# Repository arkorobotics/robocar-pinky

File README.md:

# Robocar - Pinky	

## Intro
Pinky is a 1/16 scale DIY autonomous car designed to compete in the [DIY Robocar](https://diyrobocars.com) race. Pinky also has a counterpart testbed named [Brain](Brain).

## Design

### Block Diagram

### Assembled Hardware

## Software

See the [Software](./Software) subfolder.

## Hardware

### Perception System
Part | Cost  |  Link
------------ | ------------- | -------------
ZED Mini | $399.00 | [Stereo Labs Store](https://store.stereolabs.com/products/zed-mini)
IMX219 Camera Module (Fisheye) | $29.99  | [Amazon](https://www.amazon.com/gp/product/B07VFFRX4C)

### Compute Element
Part | Cost  |  Link
------------ | ------------- | -------------
NVIDIA Jetson Nano Developer Kit | $98.98 | [Amazon](https://www.amazon.com/gp/product/B07PZHBDKT/)
Intel Dual Band Wireless-Ac 8265 w/ BT Module | $21.55 | [Amazon](https://www.amazon.com/Intel-Dual-Band-Wireless-Ac-8265/dp/B01MZA1AB2)
Noctua Fan | $14.95 | [Amazon](https://www.amazon.com/gp/product/B071FNHVXN)

### Hardware Interface Board
Part | Cost  |  Link
------------ | ------------- | -------------
Glue Board (Fab/Assembly Required) | ~$300.00 | [GitHub](./Electronics/Glue%20Board)

### Drive System
Part | Cost  |  Link
------------ | ------------- | -------------
VATOS RC Car 9137R | $54.99 | [Amazon](https://www.amazon.com/gp/product/B07QRRJZDG/)

### Chassis
Part | Cost | Link
------------ | ------------- | -------------
Screw Set | $20.98 | [Amazon](https://www.amazon.com/gp/product/B07QLWPJKC/)
Threaded Heat Insert | $19.99 | [Amazon](https://www.amazon.com/gp/product/B07MWBJB67)
3D Printable Models (Fab/Assembly Required) | ~$20.00 | [GitHub](./Mechanical/CAD/STL%20Files)

### Other
Part | Cost  |  Link
------------ | ------------- | -------------
ENGPOW 7.4V 3000mah 30C Lipo Battery | $22.99 | [Amazon](https://www.amazon.com/gp/product/B075QDPSDQ/)
Samsung SD Car 128GB | $16.99 | [Amazon](https://www.amazon.com/gp/product/B06XWZWYVP/)
1.5 ft/50cm Micro USB 3.0 Cable | $8.79 | [Amazon](https://www.amazon.com/gp/product/B075CL915V/)
5V/4A 20W Switching Power | $8.99 | [Amazon](https://www.amazon.com/gp/product/B01N4HYWAM/)
WiFi/BT Antennas | $13.99 | [Amazon](https://www.amazon.com/gp/product/B01E29566W/)
USB 3.1 Right Angle A to Right Angle C | $19.25 | [UsbFirewire](https://www.usbfirewire.com/parts/rr-arch-xxg.html#RR-ARCH-10GRC)

### Harnessing

## Assembly

For 3D printed models, use the [Autodesk Fusion 360 Pinky CAD](./Mechanical/CAD/Pinky%20Assembly%20v27.f3z) model for assembly.

For electrical assembly, see diagram below:

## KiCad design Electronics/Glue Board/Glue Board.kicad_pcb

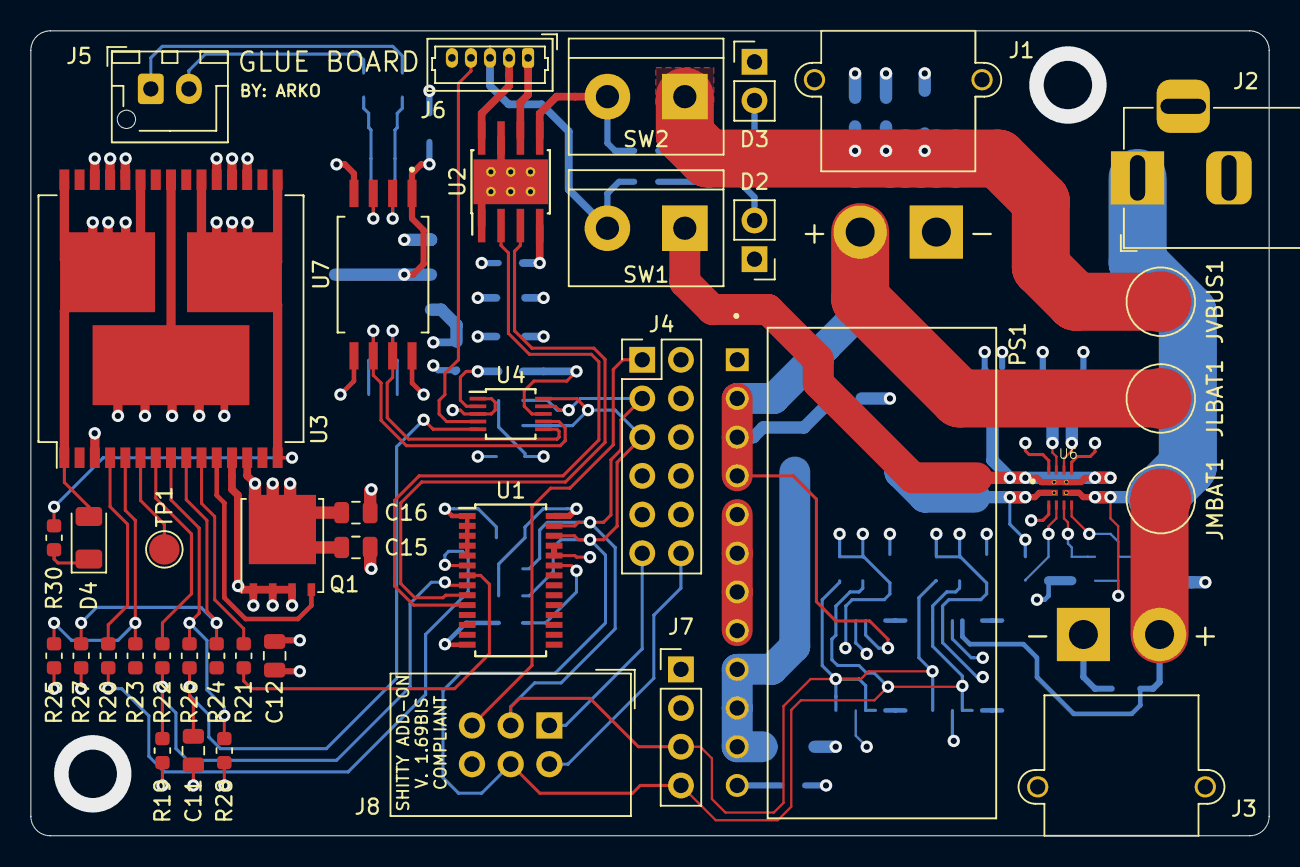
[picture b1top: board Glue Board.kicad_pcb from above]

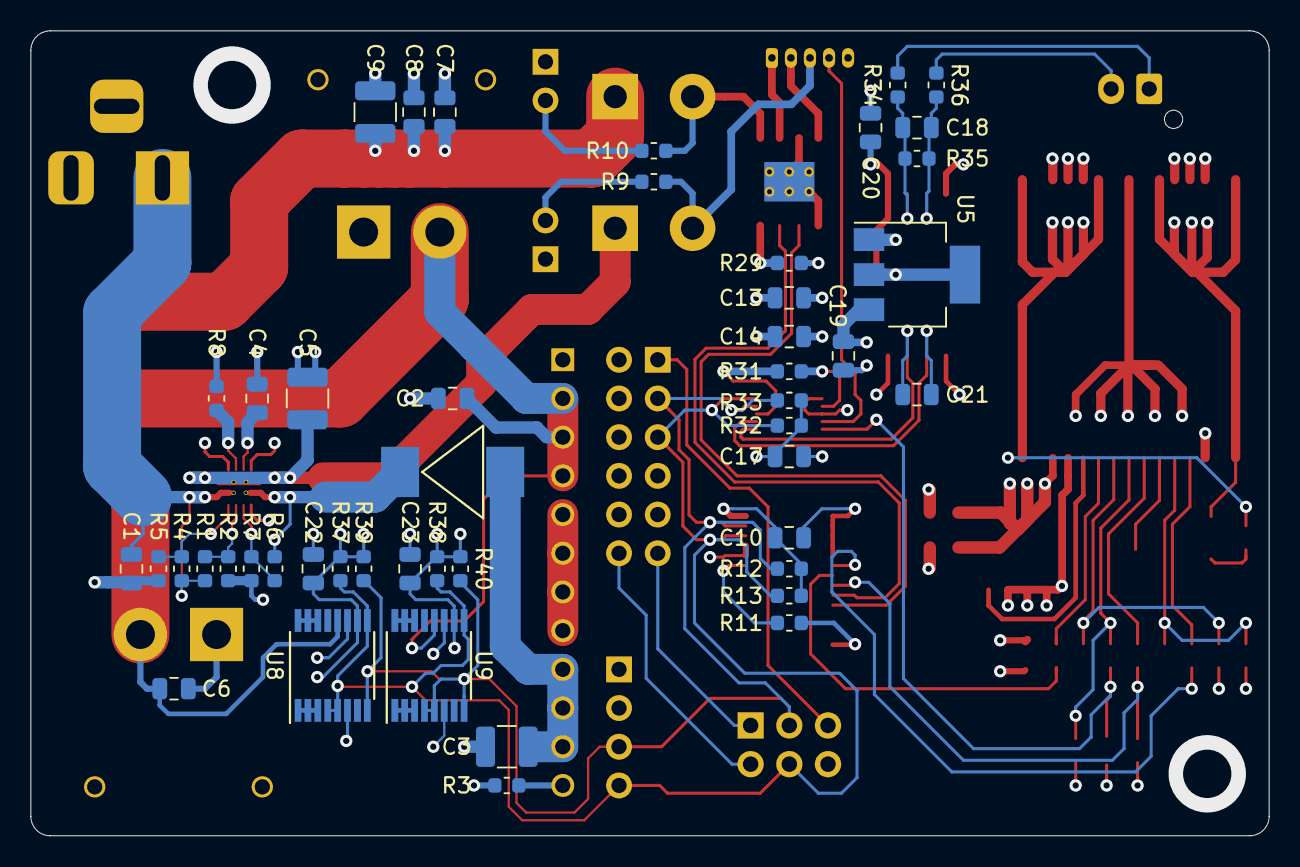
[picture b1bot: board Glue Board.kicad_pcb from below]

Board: 4 copper layers, 81.3 x 52.8 mm, 87 parts (47 on the bottom side), 56 nets.

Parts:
C1, C2, C4, C6, C7, C17, C22, C23: 1uF; C_0805_2012Metric
C3, C5, C9: 100uF; C_1210_3225Metric
C8, C19, C20: 10uF; C_0805_2012Metric
C10, C12, C14, C16: 0.1uF; C_0805_2012Metric
C11, C18, C21: 33nF; C_0805_2012Metric
C13: 22uF; C_0805_2012Metric
C15: 47uF; C_0805_2012Metric
D1: STPS5L60S; DO-214AB-SMC
D2, D3: LED; PinHeader_1x02_P2.54mm_Vertical
D4: LED_Dual_2pin; LED_1206_3216Metric
J1, J3: Conn_01x02_Male; AMASS_XT30PW-M_1x02_P2.50mm_Horizontal
J2: Barrel_Jack; BarrelJack_Horizontal
J4: Conn_02x06_Odd_Even; PinHeader_2x06_P2.54mm_Vertical
J5: Conn_01x02_Male; JST_XH_B2B-XH-AM_1x02_P2.50mm_Vertical
J6: Conn_01x05_Female; Molex_PicoBlade_53047-0510_1x05_P1.25mm_Vertical
J7: Conn_01x04_Male; PinHeader_1x04_P2.54mm_Vertical
J8: Conn_02x03_Odd_Even; IDC-Header_2x03_P2.54mm_Vertical
JLBAT1: TestPoint; TestPoint_Pad_D4.0mm
JMBAT1: TestPoint; TestPoint_Pad_D4.0mm
JVBUS1: TestPoint; TestPoint_Pad_D4.0mm
PS1: R-745.0D; CONV_R-745.0D
Q1: CSD17501Q5A; TDSON-8-1
R1, R6: 23.7k; R_0603_1608Metric
R2, R5, R7: 5k; R_0603_1608Metric
R3: 2.6k; R_0603_1608Metric
R4: 10.2k; R_0603_1608Metric
R8: 18.7k; R_0603_1608Metric
R9: 47R; R_0603_1608Metric
R10: 470; R_0603_1608Metric
R11, R12, R13, R19, R26, R31, R32, R33, R34, R36, R37, R38, R39, R40: 10k; R_0603_1608Metric
R20, R21, R22, R23, R24, R28: 1k; R_0603_1608Metric
R25, R27, R30: 4.7k; R_0603_1608Metric
R29: 30K; R_0603_1608Metric
R35: 470R; R_0603_1608Metric
SW1, SW2: SW_SPST; TerminalBlock_bornier-2_P5.08mm
TP1: TestPoint; TestPoint_Pad_D2.0mm
U1: PCA9685PW; TSSOP-28_4.4x9.7mm_P0.65mm
U2: DRV8871DDA; Texas_HTSOP-8-1EP_3.9x4.9mm_P1.27mm_EP2.95x4.9mm_Mask2.4x3.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
U3: VNH5019ATR-E; ST_MultiPowerSO-30
U4: ADS1115IDGS; TSSOP-10_3x3mm_P0.5mm
U5: NCP1117-5.0_SOT223; SOT-223-3_TabPin2
U6: TPS2121RUXR; IC_TPS2121RUXR
U7: AMC1301DWVR; SOIC127P1150X280-8N
U8, U9: INA260; TSSOP-16_4.4x5mm_P0.65mm

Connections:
+3.3V: J4.1, J8.5
+5V: C10.1, C17.1, C22.1, C23.1, J4.2, J4.4, J6.3, J7.1, R9.1, R12.1, R13.1, R25.1, R27.1, R31.1, R32.1, R33.1, R37.1, R38.1, R39.1, R40.1, SW1.2, U1.28, U4.8, U7.8, U8.10, U9.10
+5VA: C20.1, U5.2, U7.1
DRIVE_CS_ADC: C11.1, R26.2, U4.5
DRIVE_PWM: R19.1, R22.2, U1.8
GND: C1.2, C2.2, C3.2, C4.2, C5.2, C6.2, C7.2, C8.2, C9.2, C10.2, C11.2, C12.2, C13.2, C14.2, C15.2, C16.2, C17.2, C19.2, C20.2, C22.2, C23.2, D2.1, D3.1, J1.1, J2.2, J3.1, J4.6, J4.9, J6.5, J7.2, J8.6, PS1.5, PS1.6, PS1.7, PS1.8, R2.2, R3.2, R5.2, R7.2, R8.2, R11.1, R19.2, R28.2, R29.2, U1.1, U1.2, U1.3, U1.4, U1.5, U1.14, U1.24, U1.25, U2.1, U2.7, U2.9, U3.18, U3.19, U3.20, U3.26, U3.27, U3.28, U4.1, U4.3, U5.1, U6.3, U6.9, U6.12, U7.4, U7.5, U8.6, U8.11, U9.6, U9.11
GPIO50: J4.11, J8.1
GPIO79: J4.12, J8.2
IN1: U1.9, U2.3
IN2: U1.10, U2.2
INA: R20.2, U1.6
INB: R21.2, U1.7
unnamed: C1.1, J2.1, R1.1, R4.1, U6.7, U6.7_1
unnamed: C3.1, D1.2, PS1.9, PS1.10, PS1.11
unnamed: C4.1, U6.11
unnamed: C5.1, SW1.1, U6.1, U6.1_1, U6.8, U6.8_1
unnamed: C7.1, C8.1, C9.1, JVBUS1.1, SW2.1
unnamed: C18.1, R34.2, R35.1, U7.2
unnamed: C18.2, R35.2, R36.1, U7.3
unnamed: D1.1, R6.1, U6.2, U6.2_1
unnamed: D2.2, R9.2
unnamed: D3.2, R10.2
unnamed: D4.1, R30.1
unnamed: J6.1, U2.6
unnamed: J6.2, U2.8
unnamed: PS1.12, R3.1
unnamed: Q1.4, U3.11
unnamed: R1.2, R2.1, U6.5
unnamed: R4.2, R5.1, U6.6
unnamed: R6.2, R7.1, U6.4
unnamed: R8.1, U6.10
unnamed: R11.2, U1.23
unnamed: R20.1, U3.4
unnamed: R21.1, U3.10
unnamed: R22.1, U3.7
unnamed: R23.1, R25.2, U3.5
unnamed: R24.1, R27.2, U3.9
unnamed: R26.1, R28.1, U3.8
unnamed: R29.1, U2.4
unnamed: R31.2, U4.2
unnamed: TP1.1, U3.6
unnamed: U8.1, U8.2, U8.3
unnamed: U8.14, U8.15, U8.16
unnamed: U9.1, U9.2, U9.3
unnamed: U9.14, U9.15, U9.16
OUTA: D4.2, J5.1, R34.1, U3.1, U3.25, U3.30, U3.33
OUTB: J5.2, R30.2, R36.2, U3.15, U3.16, U3.21, U3.32
SCL: J4.5, J7.4, J8.4, R13.2, R32.2, R37.2, R38.2, U1.26, U4.10, U8.4, U8.5, U8.9, U9.9
SDA: J4.3, J7.3, J8.3, R12.2, R33.2, R39.2, R40.2, U1.27, U4.9, U8.8, U9.4, U9.5, U9.8
STEERING_POS_ADC: J6.4, U4.4
VBUS: C12.1, C13.1, C14.1, C19.1, Q1.1, Q1.2, Q1.3, R10.1, SW2.2, U2.5, U3.12, U5.3
VCC: C15.1, C16.1, Q1.5, U3.3, U3.13, U3.23, U3.31
VLOGIC_BAT: C2.1, J1.2, JLBAT1.1, PS1.2, PS1.3, PS1.4, U9.12
VMOTOR_BAT: C6.1, J3.2, JMBAT1.1, U8.12
VMOTOR_N_ADC: C21.2, U4.7, U7.6
VMOTOR_P_ADC: C21.1, U4.6, U7.7

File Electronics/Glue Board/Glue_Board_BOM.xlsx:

Reference | Quantity | Value | Footprint | Datasheet | MPN
C11 C18 C21 | 3 | 33nF | Capacitor_SMD:C_0805_2012Metric | ~ | C0805C333K5RACTU
C13 | 1 | 22uF | Capacitor_SMD:C_1210_3225Metric | ~ | C1210C226K3PACTU
C15 | 1 | 47uF | Capacitor_SMD:C_1210_3225Metric | ~ | GRM32EC81C476KE15L
C16 C12 C14 C10 | 4 | 0.1uF | Capacitor_SMD:C_0805_2012Metric | ~ | C0805C104Z5VACTU
C4 C1 C2 C7 C6 C17 C23 C22 | 8 | 1uF | Capacitor_SMD:C_0805_2012Metric | ~ | C0805C105K4RACTU
C5 C3 C9 | 3 | 100uF | Capacitor_SMD:C_1210_3225Metric | ~ | C1210C107M4PAC7800
C8 C20 C19 | 3 | 10uF | Capacitor_SMD:C_0805_2012Metric | ~ | C0805C106K4PACTU
D1 | 1 | STPS5L60S | agg:DO-214AB-SMC | ~ | STPS5L60S
D2 | 1 | LED | Connector_PinHeader_2.54mm:PinHeader_1x02_P2.54mm_Vertical | ~ | MPR3BWD
D3 | 1 | LED | Connector_PinHeader_2.54mm:PinHeader_1x02_P2.54mm_Vertical | ~ | MPR3RD
D4 | 1 | LED_Dual_2pin | LED_SMD:LED_1206_3216Metric | ~ | LTST-C235KGKRKT
J1 J3 | 2 | Conn_01x02_Male | Connector_AMASS:AMASS_XT30PW-M_1x02_P2.50mm_Horizontal | ~ | XT30PW-M
J2 | 1 | Barrel_Jack | Connector_BarrelJack:BarrelJack_Horizontal | ~ | PJ-102B
J4 | 1 | Conn_02x06_Odd_Even | Connector_PinHeader_2.54mm:PinHeader_2x06_P2.54mm_Vertical | ~ | 67997-112HLF
J5 | 1 | Conn_01x02_Male | Connector_JST:JST_XH_B2B-XH-AM_1x02_P2.50mm_Vertical | ~ | B2B-XH-A(LF)(SN)
J6 | 1 | Conn_01x05_Female | Connector_Molex:Molex_PicoBlade_53047-0510_1x05_P1.25mm_Vertical | ~ | 530470510
J7 | 1 | Conn_01x04_Male | Connector_PinHeader_2.54mm:PinHeader_1x04_P2.54mm_Vertical | ~
J8 | 1 | Conn_02x03_Odd_Even | Connector_IDC:IDC-Header_2x03_P2.54mm_Vertical | ~ | SFH11-NBPC-D03-ST-BK
JLBAT1 JVBUS1 JMBAT1 | 3 | TestPoint | TestPoint:TestPoint_Pad_D4.0mm | ~
PS1 | 1 | R-745.0D | libs:CONV_R-745.0D | Manufacturer Recommendations | R-745.0D
Q1 | 1 | CSD17501Q5A | Package_TO_SOT_SMD:TDSON-8-1 | http://www.ti.com/lit/gpn/csd17501q5a | CSD17501Q5A
R1 R6 | 2 | 23.7k | Resistor_SMD:R_0603_1608Metric | ~ | RC0603FR-0723K7L
R10 | 1 | 470 | Resistor_SMD:R_0603_1608Metric | ~ | ESR03EZPJ471
R19 R26 R11 R13 R12 R31 R32 R33 R34 R36 R39 R37 R40 R38 | 14 | 10k | Resistor_SMD:R_0603_1608Metric | ~ | RC0603FR-0710KL
R2 R7 R5 | 3 | 5k | Resistor_SMD:R_0603_1608Metric | ~ | CR0603-FX-4991ELF
R25 R27 R30 | 3 | 4.7k | Resistor_SMD:R_0603_1608Metric | ~ | ERJ-3EKF4751V
R28 R22 R21 R20 R23 R24 | 6 | 1k | Resistor_SMD:R_0603_1608Metric | ~ | RC0603JR-071KL
R29 | 1 | 30K | Resistor_SMD:R_0603_1608Metric | ~ | ERA-3AEB303V
R3 | 1 | 2.6k | Resistor_SMD:R_0603_1608Metric | ~ | RC0603FR-072K61L
R35 | 1 | 470R | Resistor_SMD:R_0603_1608Metric | ~ | ESR03EZPJ471
R4 | 1 | 10.2k | Resistor_SMD:R_0603_1608Metric | ~ | RC0603FR-0710K2L
R8 | 1 | 18.7k | Resistor_SMD:R_0603_1608Metric | ~ | RC0603FR-0718K7L
R9 | 1 | 47R | Resistor_SMD:R_0603_1608Metric | ~ | ESR03EZPJ470
SW1 | 1 | SW_SPST | TerminalBlock:TerminalBlock_bornier-2_P5.08mm | ~ | M2011LL1W01-G
SW2 | 1 | SW_SPST | TerminalBlock:TerminalBlock_bornier-2_P5.08mm | ~ | M2011LL1W01-C
TP1 | 1 | TestPoint | TestPoint:TestPoint_Pad_D2.0mm | ~
U1 | 1 | PCA9685PW | Package_SO:TSSOP-28_4.4x9.7mm_P0.65mm | http://www.nxp.com/documents/data_sheet/PCA9685.pdf | PCA9685PW/Q900,118
U2 | 1 | DRV8871DDA | Package_SO:Texas_HTSOP-8-1EP_3.9x4.9mm_P1.27mm_EP2.95x4.9mm_Mask2.4x3.1mm_Therm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 | http://www.ti.com/lit/ds/symlink/drv8871.pdf | DRV8871DDAR
U3 | 1 | VNH5019ATR-E | Package_SO:ST_MultiPowerSO-30 | https://www.st.com/resource/en/datasheet/vnh5019a-e.pdf | VNH5019ATR-E
U4 | 1 | ADS1115IDGS | Package_SO:TSSOP-10_3x3mm_P0.5mm | http://www.ti.com/lit/ds/symlink/ads1113.pdf | ADS1115IDGSR
U5 | 1 | NCP1117-5.0_SOT223 | Package_TO_SOT_SMD:SOT-223-3_TabPin2 | http://www.onsemi.com/pub_link/Collateral/NCP1117-D.PDF | NCP1117LPST50T3G
U6 | 1 | TPS2121RUXR | libs:IC_TPS2121RUXR | TEXAS INSTRUMENTS | TPS2121RUXR
U7 | 1 | AMC1301DWVR | libs:SOIC127P1150X280-8N | TEXAS INSTRUMENTS | AMC1301DWVR
U8 U9 | 2 | INA260 | Package_SO:TSSOP-16_4.4x5mm_P0.65mm | http://www.ti.com/lit/ds/symlink/ina260.pdf | INA260AIPW

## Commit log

2019-12-26 Initial commit with block diagram
    Initial commit with block diagram
2019-12-26 Updated with block diagram and bill of materials
    Updated with block diagram and bill of materials
2019-12-27 Started "Glue Board" PCB
    Started "Glue Board" PCB
2019-12-28 Finished the schematic for the most parts
    Finished the schematic for the most parts
2019-12-29 Complete Schematic and BOM
    Complete Schematic and BOM. Next up, layout!
2019-12-30 Added Motor v-sense and battery mon. Layout time!
    Added Motor v-sense and battery mon. Layout time!
2019-12-31 Glue Board - Rev A - Production
    Glue Board - Rev A - Production
2020-01-02 added oCamS Software
2020-01-02 Failed attempted to use opencv4. Next, I'm going to try installing opencv3 and modifying the ROS example back to the original config
2020-01-05 Abandoning the oCamS stereo cam and switching to ZED Mini due to support issues with Ubuntu 18 and ROS Melodic.
2020-01-22 Abandoned oCamS for ZED Mini and updated Glue Board
    Abandoned oCamS for ZED Mini and updated Glue Board
2020-01-25 Updated Readme
    Updated Readme
2020-01-25 Fixed spacing
    Fixed spacing
2020-01-27 Added harnessing and assembly diagrams
    Added harnessing and assembly diagrams
2020-01-27 Added broken software
2020-01-27 Started rc_ctrl. Working i2c example build
2020-01-27 Clean up
2020-01-27 some repairs
2020-01-27 more repairs
2020-01-27 renaming
2020-01-27 cleaned up more
2020-01-29 Added raw open source libraries for the i2c devices
    Added raw open source libraries for the i2c devices. Next step is to modify them to work with the i2c libraries.
2020-01-31 Ported INA260 for testing
    Ported INA260 for testing
2020-02-01 Working voltage measurement using INA260 via I2C
2020-02-03 Initial attempt at porting all the i2c device libraries
    Initial attempt at porting all the i2c device libraries
2020-02-03 All i2c device libraries build and have undergone minimal testing. Next up... real testing
2020-02-05 Fixed 8bit/16bit read/write error. Next step is to propagate these changes to other functions within the project
2020-02-05 Patched the 8/16bit word issue with I2C R/W
    Patched the 8/16bit word issue with I2C R/W
2020-02-05 Working PWM. ADS1115 still giving bogus values.
2020-02-06 Working ADC1115! It was mostly a schematic error.
2020-02-06 Removed .o file...i really should add a gitignore
2020-02-06 Added schematic change notes for REV B
    Added schematic change notes for REV B
2020-02-06 Added robocar stand
    Added robocar stand
2020-02-09 Moved glue board test code into glue.c
    Moved glue board test code into glue.c. More coding/testing required.
2020-02-11 First ctrl system test
    First ctrl system test
2020-02-11 Functional wheel spin code!
2020-02-11 Modified I2C to run faster by increasing the clock speed and decreasing the delay time between r/w
2020-02-11 Updated readme to reflect changes to jetson i2c config
    Updated readme to reflect changes to jetson i2c config
2020-02-11 Updated i2c to use 100us delays
    Updated i2c to use 100us delays
2020-02-12 First attempt at making a monotonic soft timer based control loop
    First attempt at making a monotonic soft timer based control loop
2020-02-12 Taking a step back
    Taking a step back
2020-02-12 minor bug fix
2020-02-13 Here we go again...
    Here we go again...
2020-02-14 Fixed C/C++ makefile errors
2020-02-14 Compiled/running soft real time loop
2020-02-14 removed swp artifact
2020-02-14 Working 50Hz control codegit add -A!
2020-02-16 Added shared memory, but there's a lot left to do
    Added shared memory, but there's a lot left to do
2020-02-16 Added c&dh python script and demonstrated shared mem with semaphones for transfering data between ctrl and cdh
2020-02-16 A little clean up and test before major additions
    A little clean up and test before major additions
2020-02-16 Clean up complete. Next up? python decode/write/print, then PID controller
2020-02-17 Packet parsing test
    Packet parsing test
2020-02-17 Working C++/Python command/telem. Next is PID, then python overhaul to interface with user/prcp
2020-02-17 Added state machine and fault protection
    Added state machine and fault protection
2020-02-17 Basic fault protection and state machine code
2020-02-17 Fixed tabs/spacing to 4 spaces
    Fixed tabs/spacing to 4 spaces. Not sure why it took me so long to fix this...
2020-02-18 Added PID+F controllers and some input sanitization
    Added PID+F controllers and some input sanitization
2020-02-18 Fixed makefile spacing issue
2020-02-19 Added PID tuning functions and cleaned up a bit
    Added PID tuning functions and cleaned up a bit
2020-02-19 More clean up
2020-02-19 Tuned steering PID gains. May require some tweaking when driving
2020-02-19 Best steering PID gains we will get prior to track testing. Next up, calibrate drive velocity measurements and tune gains
2020-02-19 Added wire cover stl
    Added wire cover stl
2020-02-20 Velocity gains are quote unquote good enough
2020-02-21 Started perception development, ran a basic image capture test only to learn that it slows down the soft real-time control software... problems to debug
2020-02-22 Due to resource constraints the control loop freq was brought down from 50Hz to 20Hz to allow the perception system to run with interfereing with the controller. This commit contains the good-enough 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
2020-02-23 Added delay to reading the ADS1115. Previous channel values were bleeding over, so this delay fixed that. Without it, the drive velocity PID+F control goes unstable.
2020-02-23 Updated prcp to display depth map, but the window auto update needs work.
2020-02-23 First yellow line following attempt
    First yellow line following attempt
2020-02-24 Possibly ready for a drive test. Python is very messy. Needs clean up
2020-02-24 First track run at ROM! It works!
2020-02-26 Office track, EOD commit. Works fairly well, but I need a bigger track with less... yellow
2020-02-27 Doing laps in the living room but the velocity is laggy and oscillating. I think the vision system is far too slow and as a result, the steering lags significally... and it's jerky
2020-02-28 Added optimization to the control code.. not sure why I didn't do this before
2020-02-28 Porting prcp from Python to C++ for performance
    Porting prcp from Python to C++ for performance
2020-02-28 Smooth running ctrl (20Hz) and prcp (>20hz). No lane following yet, that's next
2020-02-28 Everthing but the histrogram averaging
2020-02-29 Stopping for the day. Need to figured out how to port algo written in numpy to c++ with other libs
2020-03-02 Added lane following heuristics
    Added lane following heuristics
2020-03-03 Fast running lane follow code! So much faster without python! Clean up and optimization needed
2020-03-03 Commit for the night.. need to fix the slow imshow functio
2020-03-04 Added granular lane detection and color coding, lane following based on camera velocity
2020-03-05 Doing laps with this code! Going to cleanup now...
2020-03-05 Cleaned up and parameterized the code
    Cleaned up and parameterized the code
2020-03-05 Fixed bugs
    Fixed bugs
2020-03-05 Updated readme and minor bugs
    Updated readme and minor bugs
2020-03-05 Code lock... unless a terrible bug is found
2020-03-10 Code lock from DIYRobocar March 7, 2020
    Code lock from DIYRobocar March 7, 2020
